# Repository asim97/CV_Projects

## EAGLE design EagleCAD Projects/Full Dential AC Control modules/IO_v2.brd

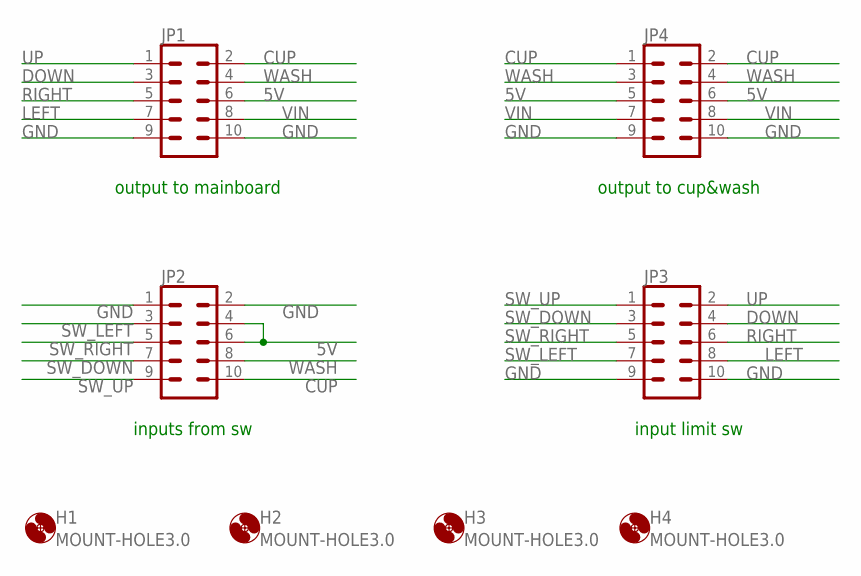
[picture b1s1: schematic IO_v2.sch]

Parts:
H1, H2, H3, H4: MOUNT-HOLE3.0; 3,0
JP1, JP2, JP3, JP4: CONN_05X2PTH; 2X5

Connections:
5V: JP1.6, JP2.4, JP2.6, JP4.5, JP4.6
CUP: JP1.2, JP2.10, JP4.1, JP4.2
DOWN: JP1.3, JP3.4
GND: JP1.9, JP1.10, JP2.1, JP2.2, JP3.9, JP3.10, JP4.9, JP4.10
LEFT: JP1.7, JP3.8
RIGHT: JP1.5, JP3.6
SW_DOWN: JP2.7, JP3.3
SW_LEFT: JP2.3, JP3.7
SW_RIGHT: JP2.5, JP3.5
SW_UP: JP2.9, JP3.1
UP: JP1.1, JP3.2
VIN: JP1.8, JP4.7, JP4.8
WASH: JP1.4, JP2.8, JP4.3, JP4.4

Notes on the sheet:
inputs from sw
output to mainboard
output to cup&wash
input limit sw

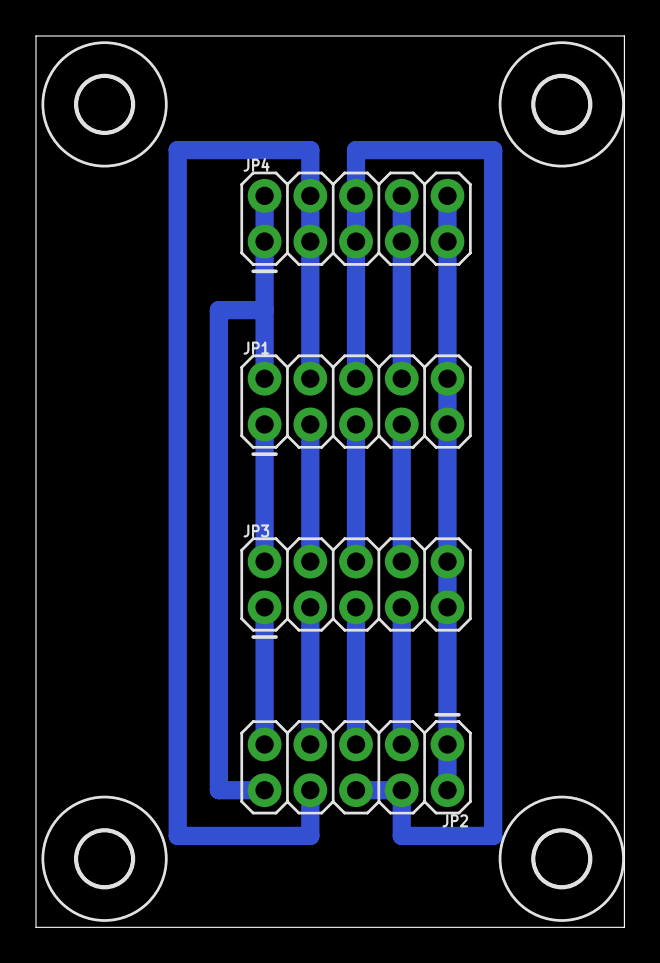
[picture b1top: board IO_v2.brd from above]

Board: 2 copper layers, 32.7 x 49.5 mm, 8 parts (0 on the bottom side), 13 nets.

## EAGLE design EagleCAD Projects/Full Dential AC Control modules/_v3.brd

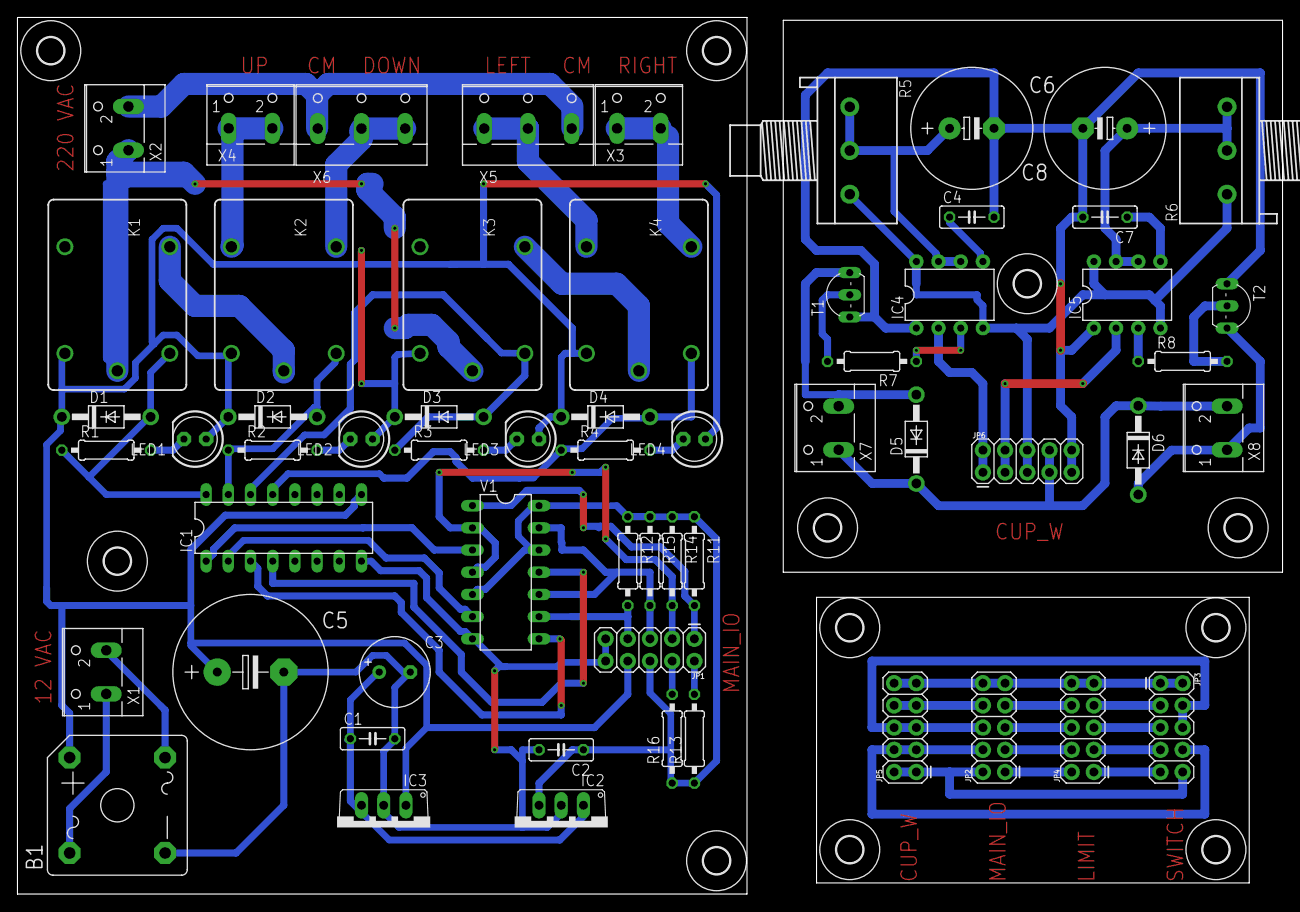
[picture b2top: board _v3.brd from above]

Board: 2 copper layers, 144.8 x 100.3 mm, 70 parts (0 on the bottom side), 60 nets.

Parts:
B1: GBPC6
C1, C2, C4, C7: 100nF; C050-025X075
C3: 10uF; E3,5-8
C5: 2200uF 50V; E7,5-18
C6, C8: 1000uF; E5-13
D1, D2, D3, D4, D5, D6: 1N4007; DO41-10
H1, H2, H3, H4, H5, H6, H7, H8, H9, H10, H11: MOUNT-HOLE3.0; 3,0
IC1: ULN2003AN; DIL16
IC2: 7805TV; TO220V
IC3: 7812TV; TO220V
IC4, IC5: NE555N; DIL08-ROUND
JP1, JP2, JP3, JP4, JP5, JP6: 2X5
K1, K2, K3, K4: JS-M1-12V-5; JS-M
LED1, LED2, LED3, LED4: LED5MM
R1, R2, R3, R4: 1K; 0207/10
R5, R6: 50K; 3RP/1610N
R7, R8: 1k; 0207/10
R11, R12, R13, R14, R15, R16: 10K; 0207/10
T1, T2: 2N2222; TO92-EBC-OVAL
V1: 7486N; DIL14
X1, X2, X3, X4, X7, X8: W237-102
X5, X6: W237-103

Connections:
5V: C2.1, IC2.3, JP1.6, R11.1, R12.1, R13.1, R14.1, R15.1, R16.1, V1.5, V1.12, V1.14
5V1: JP2.6, JP3.4, JP3.6, JP5.5, JP5.6
5V2: IC4.4, IC4.8, IC5.4, IC5.8, JP6.5, JP6.6, R5.3, R6.1
12V: C1.1, C3.+, IC2.1, IC3.3
AC1_12: B1.AC1, X1.1
AC1_220: K1.C, K3.C, X2.1
AC2_12: B1.AC2, X1.2
AC2_220: X2.2, X5.3, X6.1
CUP: JP1.2, R13.2
CUP1: JP2.2, JP3.10, JP5.1, JP5.2
CUP2: IC4.2, JP6.1, JP6.2
DOWN: JP1.3, R14.2, V1.2, V1.4
DOWN1: JP2.3, JP4.4
EN_M1: IC1.1, V1.3
EN_M1_REV: IC1.2, V1.6
EN_M2: IC1.3, V1.8
EN_M2_REV: IC1.4, V1.11
GND: B1.-, C1.2, C2.2, C3.-, C5.-, IC1.8, IC2.2, IC3.2, JP1.9, JP1.10, V1.7
GND1: JP2.9, JP2.10, JP3.1, JP3.2, JP4.9, JP4.10, JP5.9, JP5.10
GND2: C4.2, C6.-, C7.2, C8.-, IC4.1, IC5.1, JP6.9, JP6.10, T1.E, T2.E
LEFT: JP1.7, R12.2, V1.9
LEFT1: JP2.7, JP4.8
M1_DIR_EN: K1.NO, K2.C
M2_DIR_EN: K3.NO, K4.C
M_DOWN: K2.NO, X6.2, X6.3
M_LEFT: K4.NC, X5.1, X5.2
M_RIGHT: K4.NO, X3.1, X3.2
M_UP: K2.NC, X4.1, X4.2
unnamed: LED1.K, R1.2
unnamed: LED2.K, R2.2
unnamed: LED3.K, R3.2
unnamed: LED4.K, R4.2
unnamed: C4.1, IC4.5
unnamed: D5.A, T1.C, X7.2
unnamed: C7.1, IC5.5
unnamed: D6.A, T2.C, X8.1
unnamed: R7.2, T1.B
unnamed: R8.2, T2.B
OUT_CUP: IC4.3, R7.1
OUT_WASH: IC5.3, R8.1
REL_M1: D1.A, IC1.16, K1.1, R1.1
REL_M1_REV: D2.A, IC1.15, K2.1, R2.1
REL_M2: D3.A, IC1.14, K3.1, R3.1
REL_M2_REV: D4.A, IC1.13, K4.1, R4.1
RIGHT: JP1.5, R15.2, V1.10, V1.13
RIGHT1: JP2.5, JP4.6
SW_DOWN: JP3.7, JP4.3
SW_LEFT: JP3.3, JP4.7
SW_RIGHT: JP3.5, JP4.5
SW_UP: JP3.9, JP4.1
S_CUP: C6.+, IC4.6, IC4.7, R5.1, R5.2
S_WASH: C8.+, IC5.6, IC5.7, R6.2, R6.3
UP: JP1.1, R11.2, V1.1
UP1: JP2.1, JP4.2
VIN: B1.+, C5.+, D1.C, D2.C, D3.C, D4.C, IC1.9, IC3.1, JP1.8, K1.2, K2.2, K3.2, K4.2, LED1.A, LED2.A, LED3.A, LED4.A
VIN1: JP2.8, JP5.7, JP5.8
VIN2: D5.C, D6.C, JP6.7, JP6.8, X7.1, X8.2
WASH: JP1.4, R16.2
WASH1: JP2.4, JP3.8, JP5.3, JP5.4
WASH2: IC5.2, JP6.3, JP6.4

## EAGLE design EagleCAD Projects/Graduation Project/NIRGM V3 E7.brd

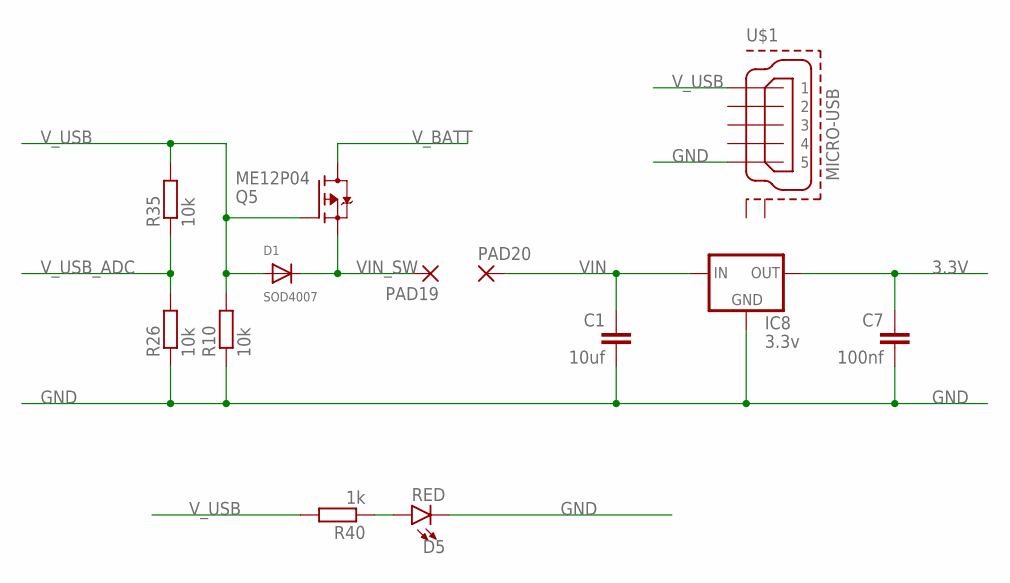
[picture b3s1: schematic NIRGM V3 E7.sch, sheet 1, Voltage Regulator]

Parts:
C1: 10uf; C1206K
C7: 100nf; C1206K
D1: SOD4007; SOD-123FL
D5: RED; LED-1206
IC8: 3.3v; TO252
PAD19, PAD20: SMD2; SMD1,27-2,54
Q5: ME12P04; TO252
R10, R26, R35: 10k; R1206
R40: 1k; R1206
U$1: MICRO-USB; 47589-0001

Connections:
3.3V: C7.1, IC8.3 (OUT); also elsewhere on the board
GND: C1.2, C7.2, D5.C, IC8.1 (GND), R10.1, R26.1, U$1.5; also elsewhere on the board
unnamed: D5.A, R40.1
VIN: C1.1, IC8.2 (IN), PAD20.1
VIN_SW: D1.C, PAD19.1, Q5.2 (S)
V_BATT: Q5.3 (D); also elsewhere on the board
V_USB: D1.A, Q5.1 (G), R10.2, R35.2, R40.2, U$1.1; also elsewhere on the board
V_USB_ADC: R26.2, R35.1; also elsewhere on the board

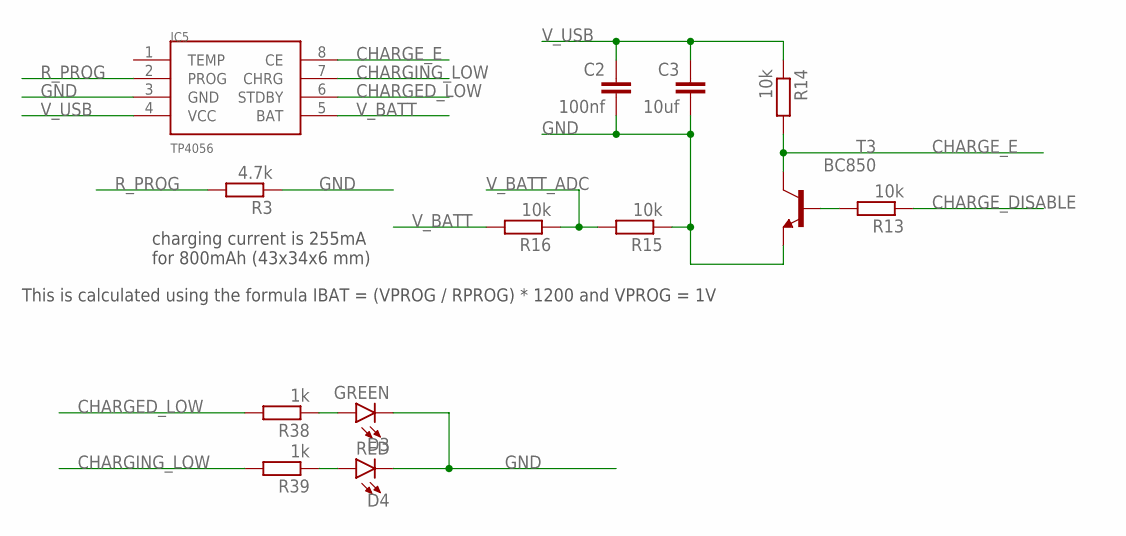
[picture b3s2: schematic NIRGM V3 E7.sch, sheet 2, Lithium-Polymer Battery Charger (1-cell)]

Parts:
C2: 100nf; C1206K
C3: 10uf; C1206K
D3: GREEN; LED-1206
D4: RED; LED-1206
IC5: TP4056; SOP-8
R3: 4.7k; R1206
R13, R14, R15, R16: 10k; R1206
R38, R39: 1k; R1206
T3: BC850; SOT23

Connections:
CHARGED_LOW: IC5.6 (STDBY), R38.2; also elsewhere on the board
CHARGE_DISABLE: R13.1; also elsewhere on the board
CHARGE_E: IC5.8 (CE), R14.2, T3.3 (C)
CHARGING_LOW: IC5.7 (CHRG), R39.2; also elsewhere on the board
GND: C2.2, C3.2, D3.C, D4.C, IC5.3 (GND), R3.1, R15.1, T3.2 (E); also elsewhere on the board
unnamed: D3.A, R38.1
unnamed: D4.A, R39.1
unnamed: R13.2, T3.1 (B)
R_PROG: IC5.2 (PROG), R3.2
V_BATT: IC5.5 (BAT), R16.2; also elsewhere on the board
V_BATT_ADC: R15.2, R16.1; also elsewhere on the board
V_USB: C2.1, C3.1, IC5.4 (VCC), R14.1; also elsewhere on the board

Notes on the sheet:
charging current is 255mA for 800mAh (43x34x6 mm)
This is calculated using the formula IBAT = (VPROG / RPROG) * 1200 and VPROG = 1V

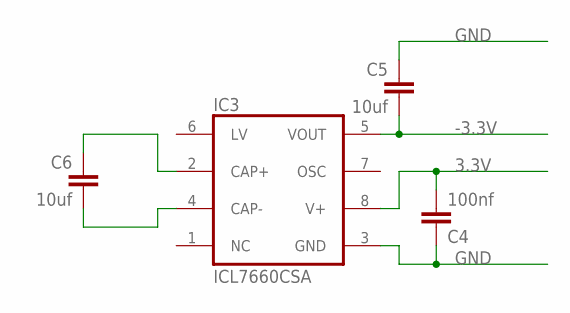
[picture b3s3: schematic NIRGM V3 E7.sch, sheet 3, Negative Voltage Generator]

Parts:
C4: 100nf; C1206K
C5, C6: 10uf; C1206K
IC3: ICL7660CSA; SO08

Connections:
3.3V: C4.2, IC3.8 (V+); also elsewhere on the board
-3.3V: C5.2, IC3.5 (VOUT); also elsewhere on the board
GND: C4.1, C5.1, IC3.3 (GND); also elsewhere on the board
unnamed: C6.1, IC3.2 (CAP+)
unnamed: C6.2, IC3.4 (CAP-)

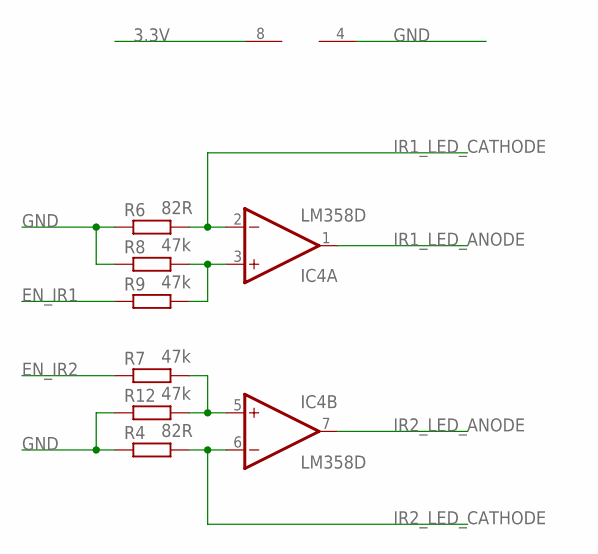
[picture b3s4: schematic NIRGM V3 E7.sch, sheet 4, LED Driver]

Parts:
IC4: LM358D; SO08
R4, R6: 82R; R1206
R7, R8, R9, R12: 47k; R1206

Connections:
3.3V: IC4.8 (V+); also elsewhere on the board
EN_IR1: R9.1; also elsewhere on the board
EN_IR2: R7.1; also elsewhere on the board
GND: IC4.4 (V-), R4.1, R6.1, R8.1, R12.1; also elsewhere on the board
IR1_LED_ANODE: IC4.1 (OUT); also elsewhere on the board
IR1_LED_CATHODE: IC4.2 (-IN), R6.2; also elsewhere on the board
IR2_LED_ANODE: IC4.7 (OUT); also elsewhere on the board
IR2_LED_CATHODE: IC4.6 (-IN), R4.2; also elsewhere on the board
unnamed: IC4.3 (+IN), R8.2, R9.2
unnamed: IC4.5 (+IN), R7.2, R12.2

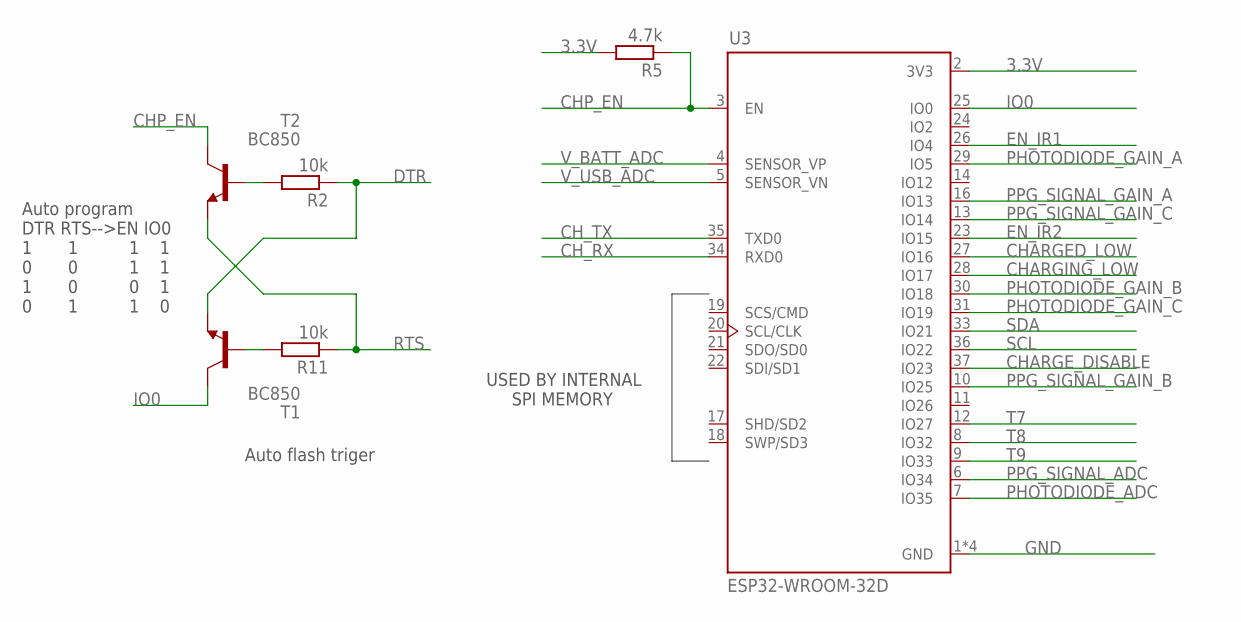
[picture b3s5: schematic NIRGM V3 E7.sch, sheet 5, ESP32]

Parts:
R2, R11: 10k; R1206
R5: 4.7k; R1206
T1, T2: BC850; SOT23
U3: ESP32-WROOM-32D; MODULE_ESP32-WROOM-32D

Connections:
3.3V: R5.2, U3.2 (3V3); also elsewhere on the board
CHARGED_LOW: U3.27 (IO16); also elsewhere on the board
CHARGE_DISABLE: U3.37 (IO23); also elsewhere on the board
CHARGING_LOW: U3.28 (IO17); also elsewhere on the board
CHP_EN: R5.1, T2.3 (C), U3.3 (EN)
CH_RX: U3.34 (RXD0); also elsewhere on the board
CH_TX: U3.35 (TXD0); also elsewhere on the board
DTR: R2.1, T1.2 (E); also elsewhere on the board
EN_IR1: U3.26 (IO4); also elsewhere on the board
EN_IR2: U3.23 (IO15); also elsewhere on the board
GND: U3.1 (GND), U3.15 (GND), U3.38 (GND), U3.39 (GND); also elsewhere on the board
IO0: T1.3 (C), U3.25 (IO0)
unnamed: R11.2, T1.1 (B)
unnamed: R2.2, T2.1 (B)
PHOTODIODE_ADC: U3.7 (IO35); also elsewhere on the board
PHOTODIODE_GAIN_A: U3.29 (IO5); also elsewhere on the board
PHOTODIODE_GAIN_B: U3.30 (IO18); also elsewhere on the board
PHOTODIODE_GAIN_C: U3.31 (IO19); also elsewhere on the board
PPG_SIGNAL_ADC: U3.6 (IO34); also elsewhere on the board
PPG_SIGNAL_GAIN_A: U3.16 (IO13); also elsewhere on the board
PPG_SIGNAL_GAIN_B: U3.10 (IO25); also elsewhere on the board
PPG_SIGNAL_GAIN_C: U3.13 (IO14); also elsewhere on the board
RTS: R11.1, T2.2 (E); also elsewhere on the board
SCL: U3.36 (IO22); also elsewhere on the board
SDA: U3.33 (IO21); also elsewhere on the board
T7: U3.12 (IO27); also elsewhere on the board
T8: U3.8 (IO32); also elsewhere on the board
T9: U3.9 (IO33); also elsewhere on the board
V_BATT_ADC: U3.4 (SENSOR_VP); also elsewhere on the board
V_USB_ADC: U3.5 (SENSOR_VN); also elsewhere on the board

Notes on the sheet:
USED BY INTERNAL SPI MEMORY
Auto flash triger
Auto program DTR RTS-->EN IO0 1 1 1 1 0 0 1 1 1 0 0 1 0 1 1 0

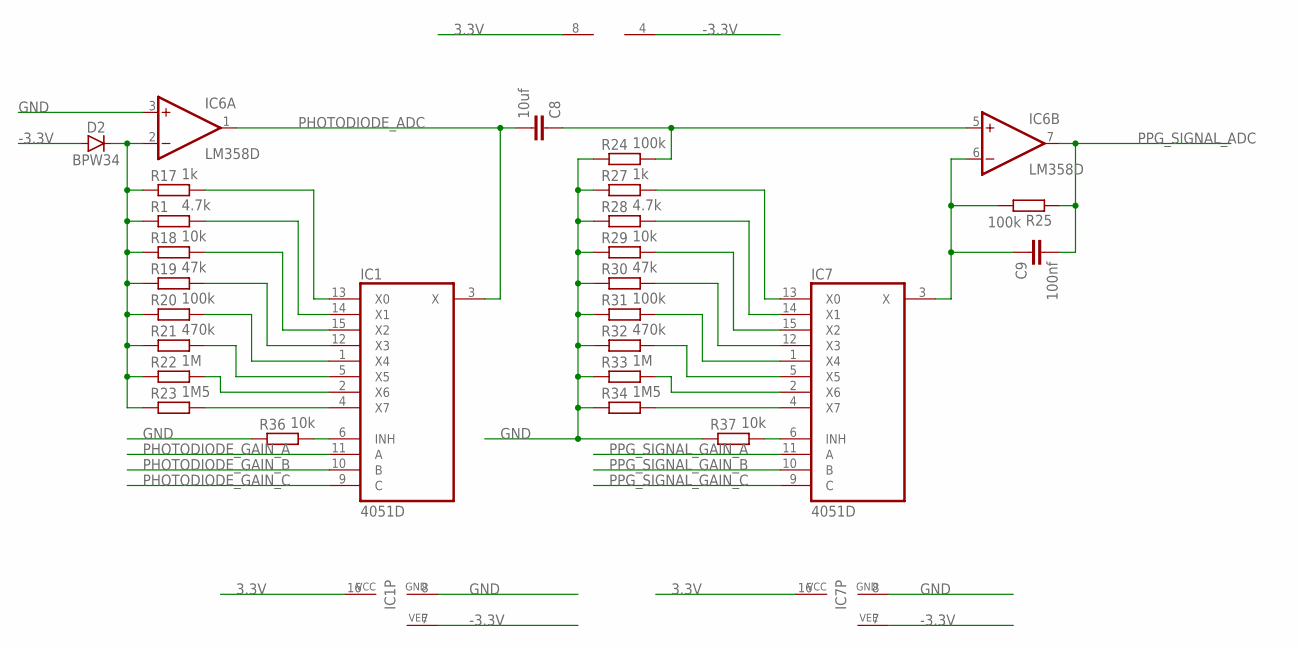
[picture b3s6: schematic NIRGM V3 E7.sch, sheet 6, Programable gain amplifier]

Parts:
C8: 10uf; C1206K
C9: 100nf; C1206K
D2: BPW34
IC1, IC7: 4051D; SO16
IC6: LM358D; SO08
R1, R28: 4.7k; R1206
R17, R27: 1k; R1206
R18, R29, R36, R37: 10k; R1206
R19, R30: 47k; R1206
R20, R24, R25, R31: 100k; R1206
R21, R32: 470k; R1206
R22, R33: 1M; R1206
R23, R34: 1M5; R1206

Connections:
3.3V: IC1.16 (VCC), IC6.8 (V+), IC7.16 (VCC); also elsewhere on the board
-3.3V: D2.P$1 (A), IC1.7 (VEE), IC6.4 (V-), IC7.7 (VEE); also elsewhere on the board
GND: IC1.8 (GND), IC6.3 (+IN), IC7.8 (GND), R24.1, R27.1, R28.1, R29.1, R30.1, R31.1, R32.1, R33.1, R34.1, R36.1, R37.1; also elsewhere on the board
unnamed: IC1.6 (INH), R36.2
unnamed: IC7.6 (INH), R37.2
unnamed: IC1.13 (X0), R17.2
unnamed: IC1.14 (X1), R1.2
unnamed: D2.P$2 (C), IC6.2 (-IN), R1.1, R17.1, R18.1, R19.1, R20.1, R21.1, R22.1, R23.1
unnamed: C8.1, IC6.5 (+IN), R24.2
unnamed: IC1.15 (X2), R18.2
unnamed: IC1.12 (X3), R19.2
unnamed: IC1.1 (X4), R20.2
unnamed: IC1.5 (X5), R21.2
unnamed: IC1.2 (X6), R22.2
unnamed: IC1.4 (X7), R23.2
unnamed: C9.1, IC6.6 (-IN), IC7.3 (X), R25.2
unnamed: IC7.13 (X0), R27.2
unnamed: IC7.14 (X1), R28.2
unnamed: IC7.15 (X2), R29.2
unnamed: IC7.12 (X3), R30.2
unnamed: IC7.1 (X4), R31.2
unnamed: IC7.5 (X5), R32.2
unnamed: IC7.2 (X6), R33.2
unnamed: IC7.4 (X7), R34.2
PHOTODIODE_ADC: C8.2, IC1.3 (X), IC6.1 (OUT); also elsewhere on the board
PHOTODIODE_GAIN_A: IC1.11 (A); also elsewhere on the board
PHOTODIODE_GAIN_B: IC1.10 (B); also elsewhere on the board
PHOTODIODE_GAIN_C: IC1.9 (C); also elsewhere on the board
PPG_SIGNAL_ADC: C9.2, IC6.7 (OUT), R25.1; also elsewhere on the board
PPG_SIGNAL_GAIN_A: IC7.11 (A); also elsewhere on the board
PPG_SIGNAL_GAIN_B: IC7.10 (B); also elsewhere on the board
PPG_SIGNAL_GAIN_C: IC7.9 (C); also elsewhere on the board

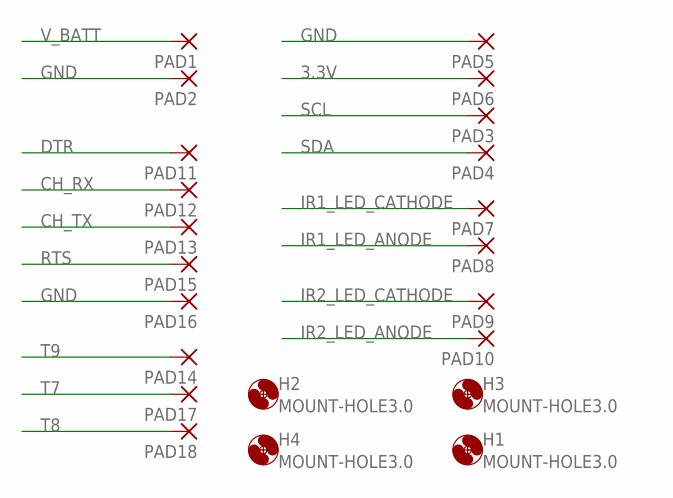
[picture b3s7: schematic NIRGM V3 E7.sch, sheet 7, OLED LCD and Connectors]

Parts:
H1, H2, H3, H4: MOUNT-HOLE3.0; 3,0
PAD1, PAD2: WIREPADSMD5-2,5; 5-2,5
PAD3, PAD4, PAD5, PAD6, PAD7, PAD8, PAD9, PAD10, PAD11, PAD12, PAD13, PAD14, PAD15, PAD16, PAD17, PAD18: SMD2; SMD1,27-2,54

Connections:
3.3V: PAD6.1; also elsewhere on the board
CH_RX: PAD12.1; also elsewhere on the board
CH_TX: PAD13.1; also elsewhere on the board
DTR: PAD11.1; also elsewhere on the board
GND: PAD2.1, PAD5.1, PAD16.1; also elsewhere on the board
IR1_LED_ANODE: PAD8.1; also elsewhere on the board
IR1_LED_CATHODE: PAD7.1; also elsewhere on the board
IR2_LED_ANODE: PAD10.1; also elsewhere on the board
IR2_LED_CATHODE: PAD9.1; also elsewhere on the board
RTS: PAD15.1; also elsewhere on the board
SCL: PAD3.1; also elsewhere on the board
SDA: PAD4.1; also elsewhere on the board
T7: PAD17.1; also elsewhere on the board
T8: PAD18.1; also elsewhere on the board
T9: PAD14.1; also elsewhere on the board
V_BATT: PAD1.1; also elsewhere on the board

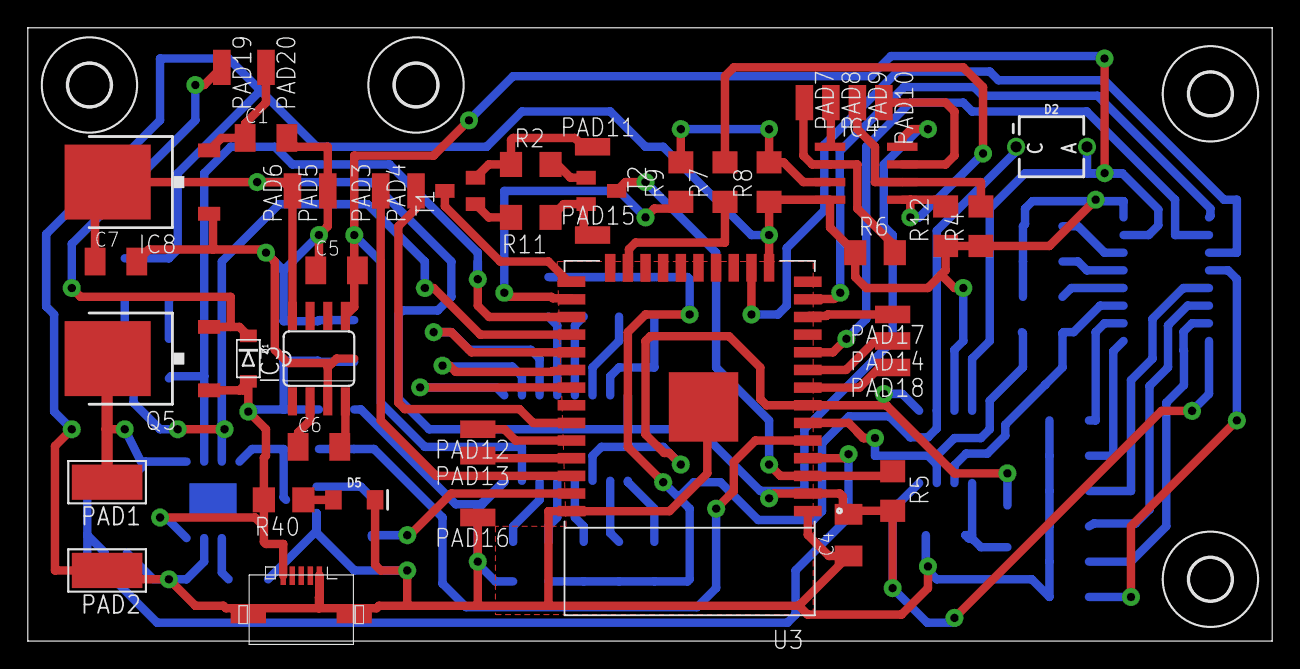
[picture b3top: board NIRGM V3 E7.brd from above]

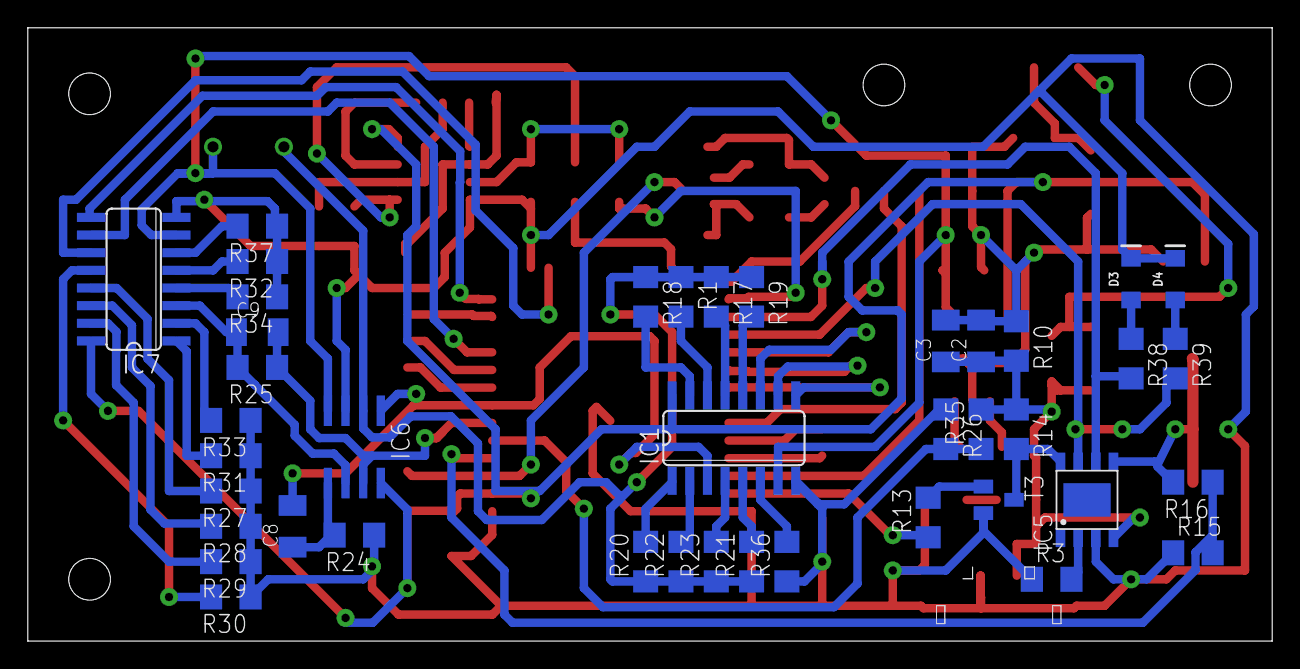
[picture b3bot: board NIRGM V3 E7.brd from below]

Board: 2 copper layers, 89.5 x 44.1 mm, 91 parts (41 on the bottom side), 70 nets.

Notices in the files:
parts and their libraries:
SparkFun-Connectors: Licensing: Creative Commons ShareAlike 4.0 International - https://creativecommons.org/licenses/by-sa/4.0
con-molex-usb: (C) 2014 Tomasz Boleslaw CEDRO, cederom@tlen.pl, http://www.tomek.cedro.info.
